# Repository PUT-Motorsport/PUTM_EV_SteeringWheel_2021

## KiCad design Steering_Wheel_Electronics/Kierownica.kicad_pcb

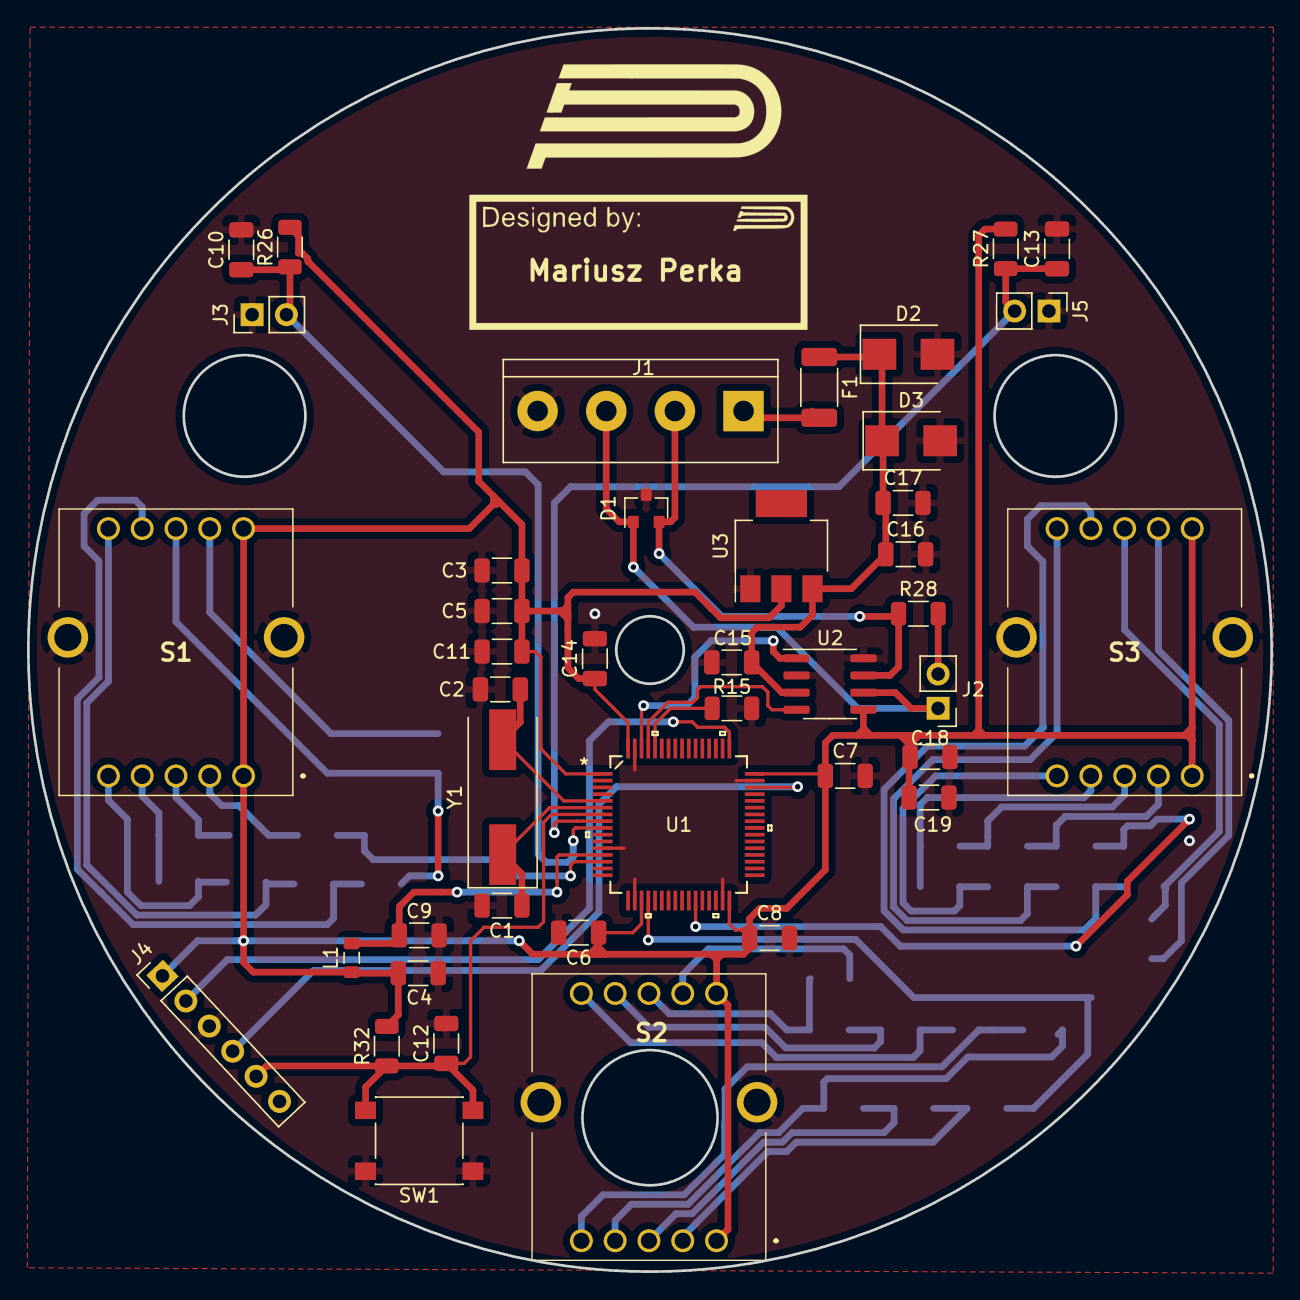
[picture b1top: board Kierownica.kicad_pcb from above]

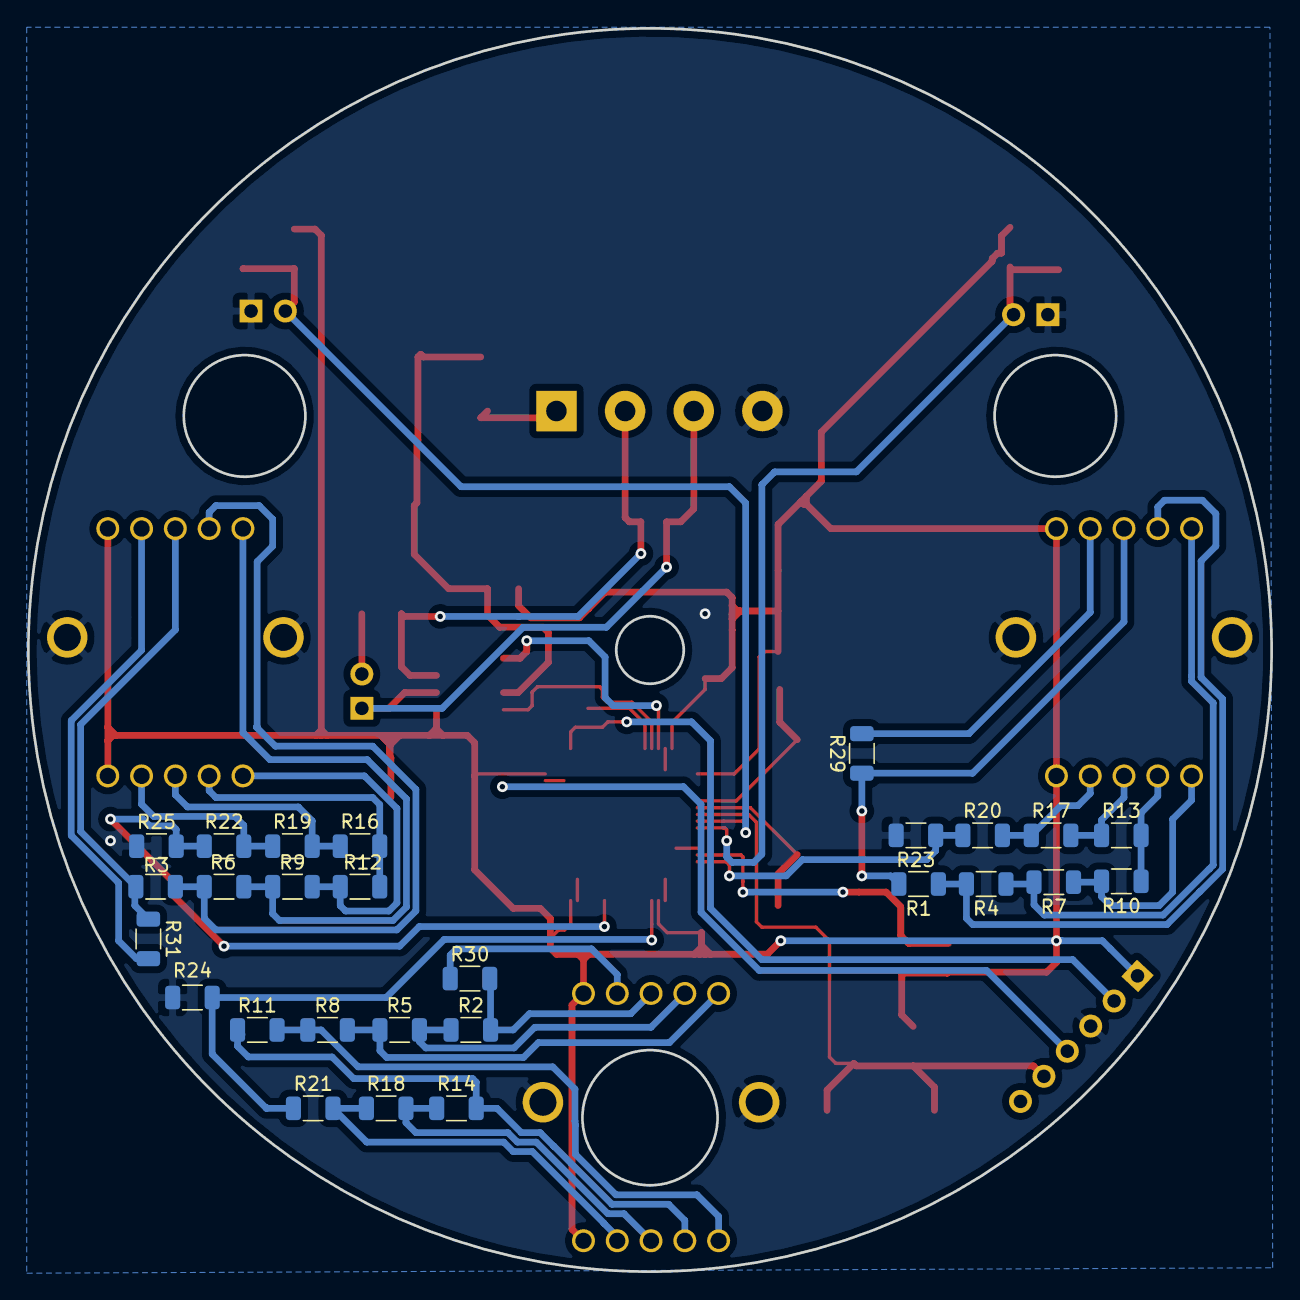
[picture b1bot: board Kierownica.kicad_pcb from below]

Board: 2 copper layers, 92.0 x 92.0 mm, 69 parts (27 on the bottom side), 45 nets.

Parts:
C1, C2: 20pF; C_1206_3216Metric
C3, C16, C19: 1uF; C_1206_3216Metric
C4: 10nF; C_1206_3216Metric
C5: 4,7uF; C_1206_3216Metric
C6, C7, C8, C9, C10, C11, C13, C14, C15, C17, C18: 100nF; C_1206_3216Metric
C12: 0.1uF; C_1206_3216Metric
D1: D_TVS_x2_AAC; SOT-23
D2: D_Schottky; D_SMB
D3: 5V; D_SMB
F1: Fuse; Fuse_2010_5025Metric
J1: Conn_01x04_Male; TerminalBlock_bornier-4_P5.08mm
J2, J3, J5: Conn_01x02_Male; PinHeader_1x02_P2.54mm_Vertical
J4: Conn_01x06_Male; PinHeader_1x06_P2.54mm_Vertical
L1: 10uH; L_0805_2012Metric
R1, R2, R3: 2k2; R_1206_3216Metric
R4, R5, R6: 910R; R_1206_3216Metric
R7, R8, R9: 510R; R_1206_3216Metric
R10, R11, R12: 330R; R_1206_3216Metric
R13, R14, R16: 220R; R_1206_3216Metric
R15, R32: 100k; R_1206_3216Metric
R17, R18, R19: 170R; R_1206_3216Metric
R20, R21, R22: 100R; R_1206_3216Metric
R23, R24, R25: 1k; R_1206_3216Metric
R26, R27: 10k; R_1206_3216Metric
R28: 120R; R_1206_3216Metric
R29, R30, R31: 11k; R_1206_3216Metric
S1, S2, S3: SR17A1815F89N
SW1: SW_Push; SW_Push_1P1T_NO_6x6mm_H9.5mm
U1: STM32L4P5RET6
U2: MCP2562-H-SN; SOIC-8_3.9x4.9mm_P1.27mm
U3: LM1117-3.3; SOT-223
Y1: 16MHz; Crystal_SMD_HC49-SD

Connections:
+5V: C15.1, C16.1, C17.1, D2.1, D3.1, F1.1, U2.3, U3.3
CANH: D1.2, J1.2, R28.1, U2.7
CANL: D1.1, J1.3, J2.1, U2.6
NRST: C12.1, J4.5, R32.1, SW1.2, U1.7
unnamed: C1.1, U1.6, Y1.1
unnamed: C2.1, U1.5, Y1.2
unnamed: C9.2, L1.2, U1.13
unnamed: C10.1, J3.2, R26.1, U1.9
unnamed: C13.1, J5.2, R27.1, U1.8
unnamed: J2.2, R28.2
unnamed: R1.1, R4.2, S1.7
unnamed: R1.2, R29.1, S1.8
unnamed: R2.1, R5.2, S2.7
unnamed: R2.2, R30.1, S2.8
unnamed: R3.1, R6.2, S3.7
unnamed: R3.2, R31.1, S3.8
unnamed: R4.1, R7.2, S1.6
unnamed: R5.1, R8.2, S2.6
unnamed: R6.1, R9.2, S3.6
unnamed: R10.1, R13.2, S1.4
unnamed: R7.1, R10.2, S1.5
unnamed: R11.1, R14.2, S2.4
unnamed: R8.1, R11.2, S2.5
unnamed: R12.1, R16.2, S3.4
unnamed: R9.1, R12.2, S3.5
unnamed: R13.1, R17.2, S1.3
unnamed: R14.1, R18.2, S2.3
unnamed: R15.2, U1.60
unnamed: R16.1, R19.2, S3.3
unnamed: R17.1, R20.2, S1.2
unnamed: R18.1, R21.2, S2.2
unnamed: R19.1, R22.2, S3.2
unnamed: R20.1, R23.1, U1.14
unnamed: R21.1, R24.1, U1.20
unnamed: R22.1, R25.1, U1.27
unnamed: R29.2, S1.9
unnamed: R30.2, S2.9
unnamed: R31.2, S3.9
RX_Can: U1.61, U2.4
SWCLK: J4.2, U1.49
SWDIO: J4.4, U1.46
SW_GND: C1.2, C2.2, C3.2, C4.2, C5.2, C6.2, C7.2, C8.2, C9.1, C10.2, C11.1, C12.2, C13.2, C14.2, C15.2, C16.2, C17.2, C18.2, C19.2, D1.3, D2.2, D3.2, J1.4, J3.1, J4.3, J5.1, R15.1, R23.2, R24.2, R25.2, S1.MH1, S1.MH2, S2.MH1, S2.MH2, S3.MH1, S3.MH2, SW1.1, U1.12, U1.18, U1.31, U1.47, U1.63, U2.2, U2.8, U3.1
SW_VDDtarget: C3.1, C4.1, C5.1, C6.1, C7.1, C8.1, C11.2, C14.1, C18.1, C19.1, J4.1, L1.1, R26.2, R27.2, R32.2, S1.1, S1.10, S2.1, S2.10, S3.1, S3.10, U1.1, U1.19, U1.32, U1.48, U1.64, U2.5, U3.2
TX_Can: U1.62, U2.1
VCC: F1.2, J1.1

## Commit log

2021-05-26 v1.0 Steering wheel init
2021-05-27 Generated project, ioc file
2021-05-29 Added full functionality

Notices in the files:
parts and their libraries:
Copyright 2016 Accelerated Designs. All rights reserved.
